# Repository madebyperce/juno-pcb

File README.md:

# Juno rev. 1 (aka THE SNOOT BOOPER)

Juno is a one-key macropad that can be configured using QMK.

**The build guide is [located here](https://github.com/na-che-x/juno-pcb/blob/main/docs/buildguide.md).**

I set up my macropad to output a random string from a predefined list of strings. Because, why not?

## Photos of the macropad

## Photos of the muse who inspired it all

## Sample Output
RooOOOoOoooo

RooOOOoOoooo

BORK BORK

*lick*

rrrrrrrrrrrrrrrRRrrrr

rUuuUUuUUUuuuuuuuu

AWOOOOOOOOOOOOO

AWOOOOOOOOOOOOO

My name is Juno!!!!

RooOOOoOoooo

*pant pant*

rUuuUUuUUUuuuuuuuu

Sometimes my poops are soft :(

Sometimes my poops are soft :(

AWOOOOOOOOOOOOO

BORK BORK

AWOOOOOOOOOOOOO

*lick*

RooOOOoOoooo

rUuuUUuUUUuuuuuuuu

AWOOOOOOOOOOOOO

rUuuUUuUUUuuuuuuuu

rooo?

rUuuUUuUUUuuuuuuuu

rooo?

AWOOOOOOOOOOOOO

Sometimes my poops are soft :(

rrrrrrrrrrrrrrrRRrrrr

AWOOOOOOOOOOOOO

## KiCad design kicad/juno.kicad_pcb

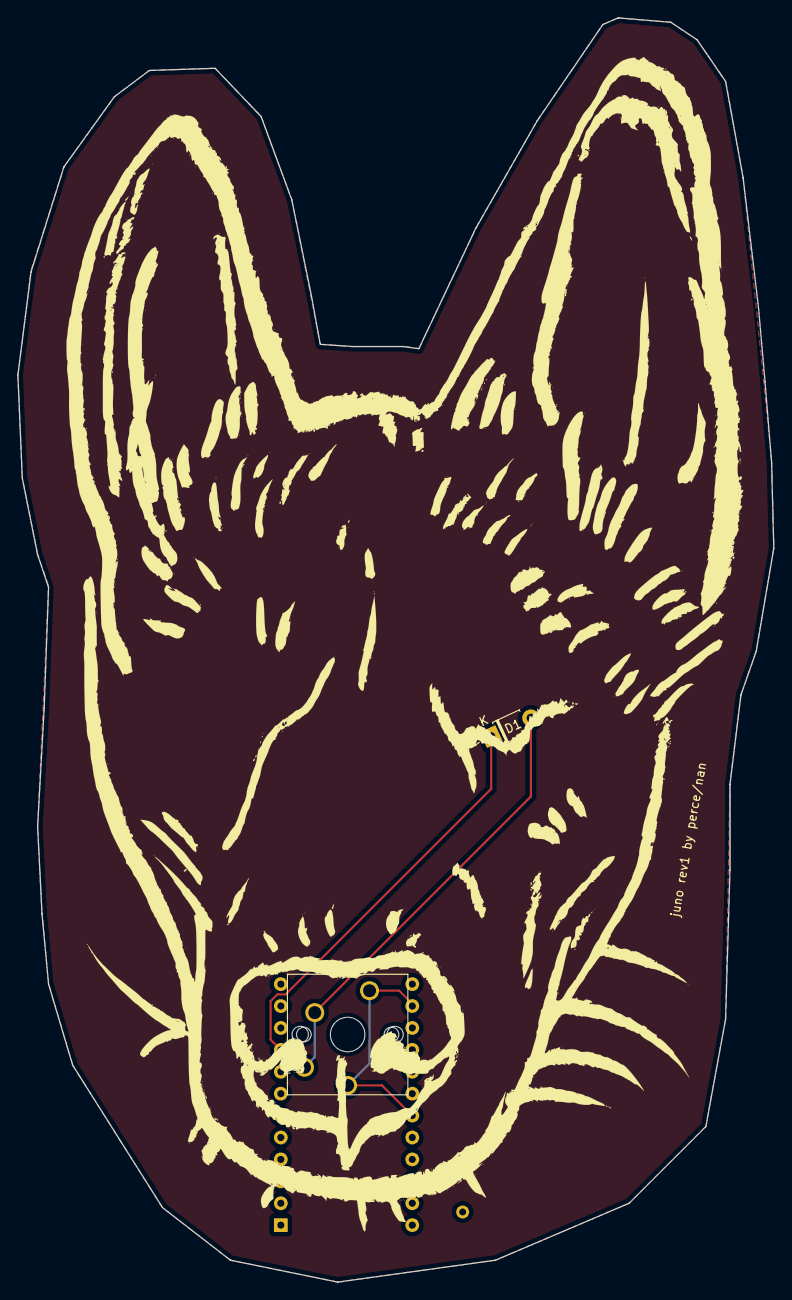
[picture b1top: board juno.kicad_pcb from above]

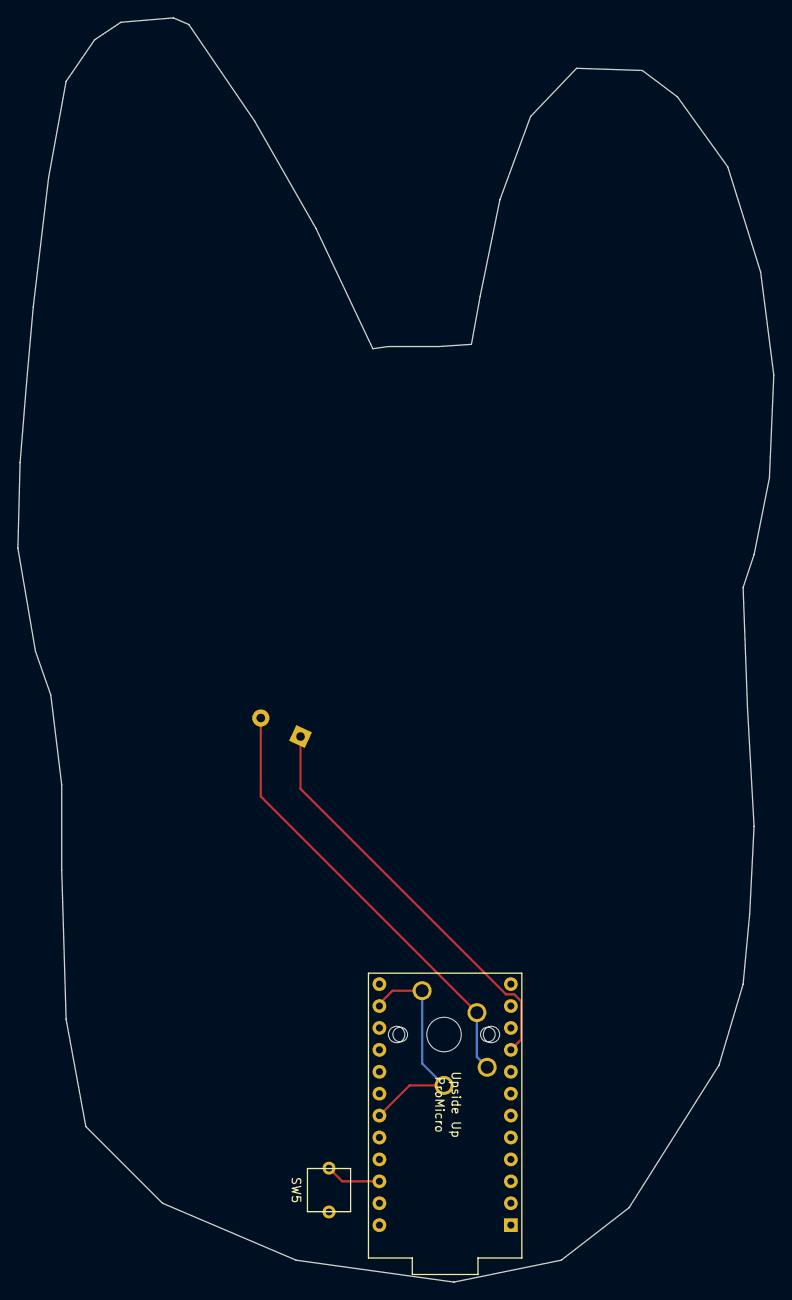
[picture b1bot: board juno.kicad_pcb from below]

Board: 2 copper layers, 87.6 x 146.6 mm, 4 parts (2 on the bottom side), 5 nets.

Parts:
D1: D_Small; D_T-1_P5.08mm_Horizontal
SW1: SW_Push; SW_Cherry_MX1A_1.00u_PCB
SW5: SW_Push; tact_switch_5mm
U1: ProMicro

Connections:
GND: SW5.2, U1.3, U1.4, U1.23
unnamed: D1.2, SW1.2
RST: SW5.1, U1.22
col0: SW1.1, U1.19
row0: D1.1, U1.9

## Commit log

2021-06-23 add some images, new subdirectories
2021-06-23 test formatting and ref to folders
2021-06-23 update docs
2021-06-23 fix links
2021-06-23 update formatting
2021-06-23 grammar
2021-06-25 add new photo!
